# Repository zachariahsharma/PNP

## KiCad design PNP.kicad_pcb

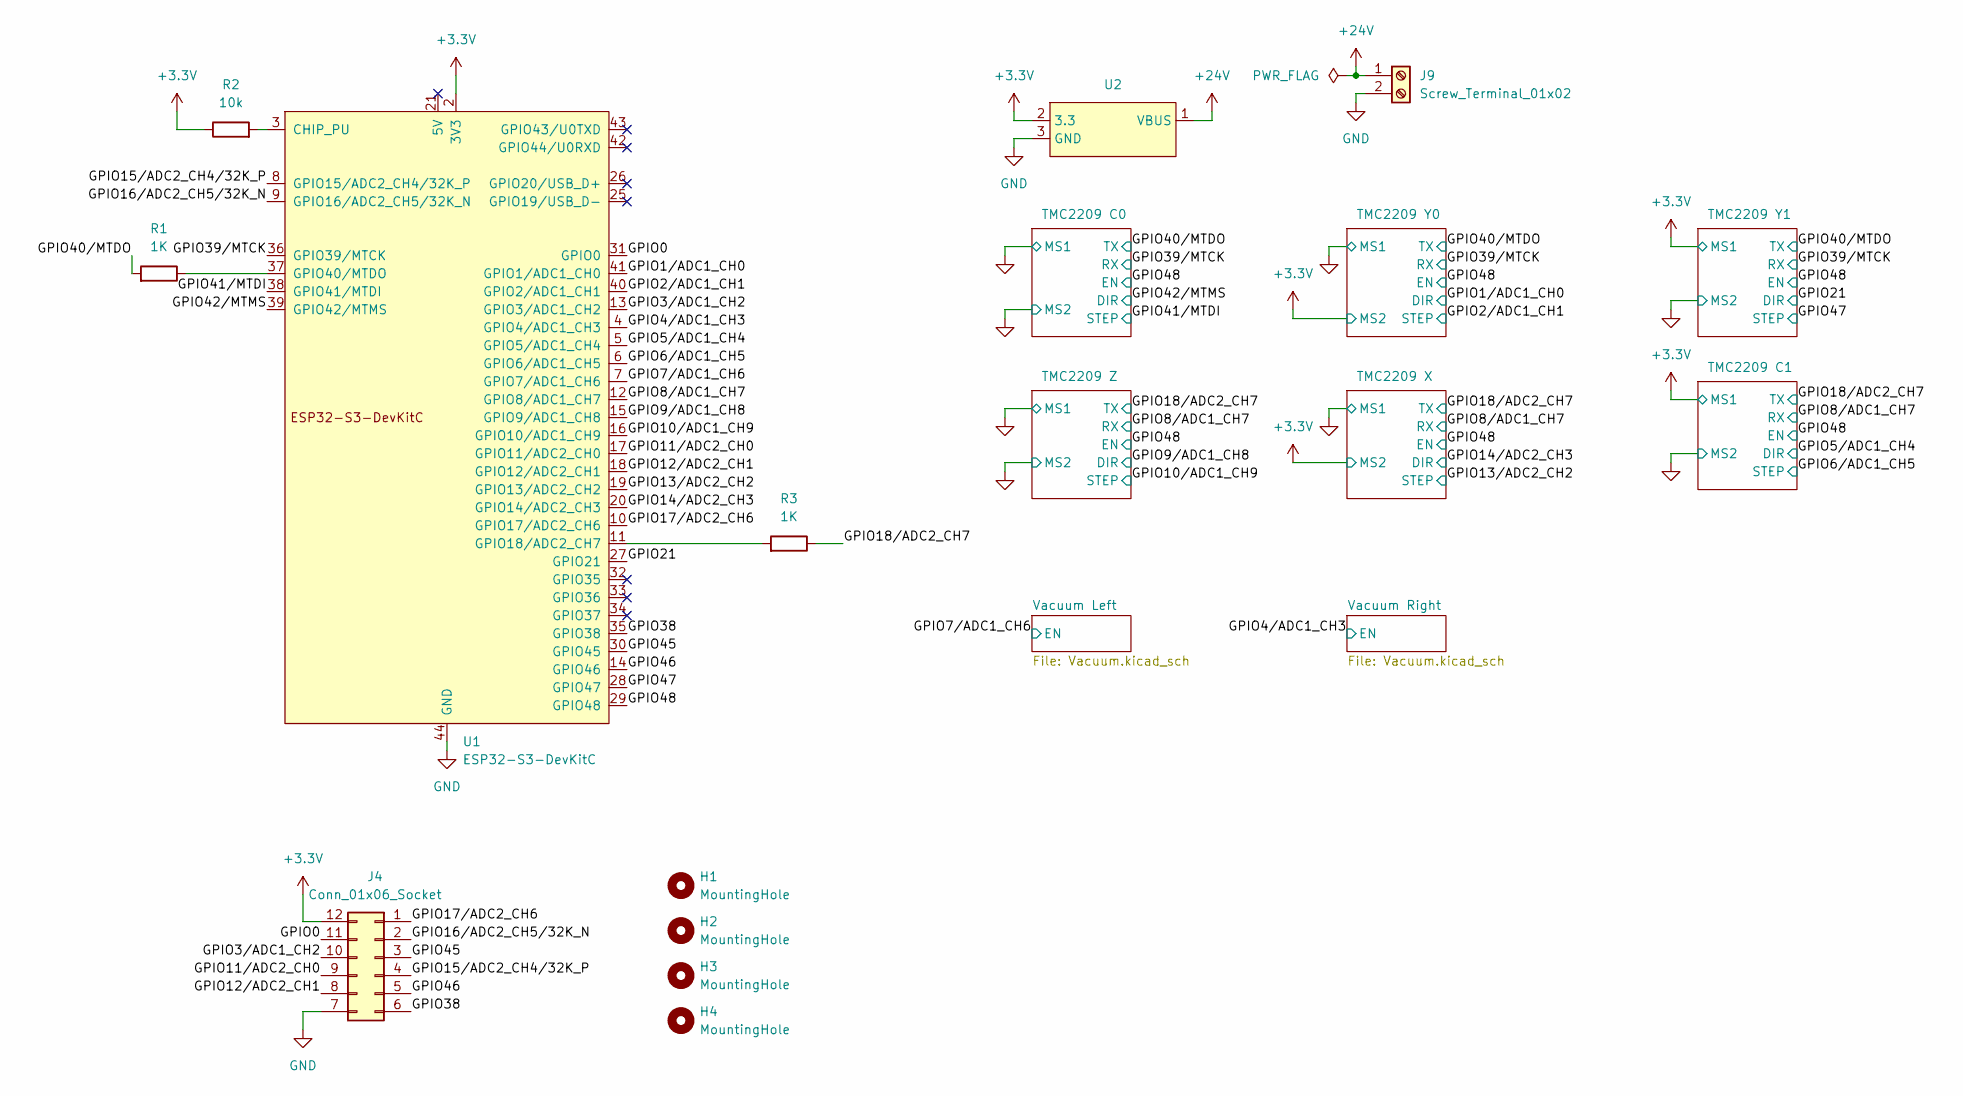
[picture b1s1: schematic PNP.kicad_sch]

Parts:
H1, H2, H3, H4: MountingHole; MountingHole_4.3mm_M4
J4: Conn_01x06_Socket; PinHeader_2x06_P2.54mm_Vertical
J9: Screw_Terminal_01x02; TerminalBlock_Phoenix_MKDS-1,5-2-5.08_1x02_P5.08mm_Horizont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
R1, R3: 1K; R_Axial_DIN0207_L6.3mm_D2.5mm_P7.62mm_Horizontal
R2: 10k; R_Axial_DIN0207_L6.3mm_D2.5mm_P7.62mm_Horizontal
U1: ESP32-S3-DevKitC
U2: Mini MP1584EN Buck Converter Module

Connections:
+3.3V: J4.12, R2.1, U1.1 (3V3), U1.2 (3V3), U2.2 (3.3); also elsewhere on the board
+24V: J9.1, U2.1 (VBUS); also elsewhere on the board
/GPIO0: J4.11, U1.31 (GPIO0)
/GPIO1/ADC1_CH0: U1.41 (GPIO1/ADC1_CH0); also elsewhere on the board
/GPIO2/ADC1_CH1: U1.40 (GPIO2/ADC1_CH1); also elsewhere on the board
/GPIO3/ADC1_CH2: J4.10, U1.13 (GPIO3/ADC1_CH2)
/GPIO4/ADC1_CH3: U1.4 (GPIO4/ADC1_CH3); also elsewhere on the board
/GPIO5/ADC1_CH4: U1.5 (GPIO5/ADC1_CH4); also elsewhere on the board
/GPIO6/ADC1_CH5: U1.6 (GPIO6/ADC1_CH5); also elsewhere on the board
/GPIO7/ADC1_CH6: U1.7 (GPIO7/ADC1_CH6); also elsewhere on the board
/GPIO9/ADC1_CH8: U1.15 (GPIO9/ADC1_CH8); also elsewhere on the board
/GPIO10/ADC1_CH9: U1.16 (GPIO10/ADC1_CH9); also elsewhere on the board
/GPIO11/ADC2_CH0: J4.9, U1.17 (GPIO11/ADC2_CH0)
/GPIO12/ADC2_CH1: J4.8, U1.18 (GPIO12/ADC2_CH1)
/GPIO13/ADC2_CH2: U1.19 (GPIO13/ADC2_CH2); also elsewhere on the board
/GPIO14/ADC2_CH3: U1.20 (GPIO14/ADC2_CH3); also elsewhere on the board
/GPIO15/ADC2_CH4/32K_P: J4.4, U1.8 (GPIO15/ADC2_CH4/32K_P)
/GPIO17/ADC2_CH6: J4.1, U1.10 (GPIO17/ADC2_CH6)
/GPIO18/ADC2_CH7: R3.1, U1.12 (GPIO8/ADC1_CH7); also elsewhere on the board
/GPIO21: U1.27 (GPIO21); also elsewhere on the board
/GPIO38: J4.6, U1.35 (GPIO38)
/GPIO39/MTCK: R1.2, U1.36 (GPIO39/MTCK); also elsewhere on the board
/GPIO41/MTDI: U1.38 (GPIO41/MTDI); also elsewhere on the board
/GPIO42/MTMS: U1.39 (GPIO42/MTMS); also elsewhere on the board
/GPIO45: J4.3, U1.30 (GPIO45)
/GPIO46: J4.5, U1.14 (GPIO46)
/GPIO47: U1.28 (GPIO47); also elsewhere on the board
/GPIO48: U1.29 (GPIO48); also elsewhere on the board
GND: J4.7, J9.2, U1.22 (GND), U1.23 (GND), U1.24 (GND), U1.44 (GND), U2.3 (GND); also elsewhere on the board
unnamed: R2.2, U1.3 (CHIP_PU)
unnamed: R3.2, U1.11 (GPIO18/ADC2_CH7)
unnamed: R1.1, U1.37 (GPIO40/MTDO)

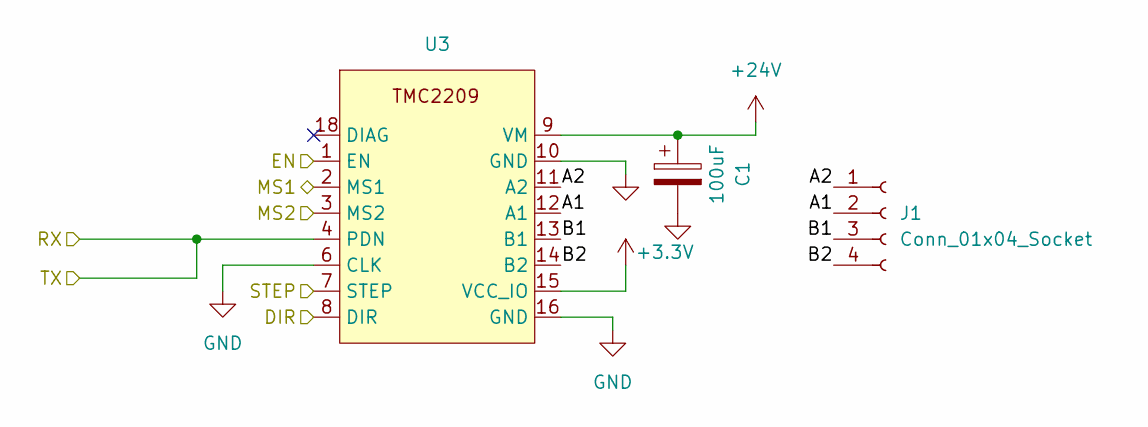
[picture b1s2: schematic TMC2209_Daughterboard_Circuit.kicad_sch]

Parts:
C1: 100uF; CP_Radial_D8.0mm_P3.50mm
J1: Conn_01x04_Socket; JST_EH_B4B-EH-A_1x04_P2.50mm_Vertical
U3: TMC2209 V1.3

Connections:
+3.3V: U3.3 (MS2), U3.15 (VCC_IO); also elsewhere on the board
+24V: C1.1, U3.9 (VM); also elsewhere on the board
/GPIO13/ADC2_CH2: U3.7 (STEP); also elsewhere on the board
/GPIO14/ADC2_CH3: U3.8 (DIR); also elsewhere on the board
/GPIO18/ADC2_CH7: U3.4 (PDN); also elsewhere on the board
/GPIO48: U3.1 (EN); also elsewhere on the board
/TMC2209 X/A1: J1.2, U3.12 (A1)
/TMC2209 X/A2: J1.1, U3.11 (A2)
/TMC2209 X/B1: J1.3, U3.13 (B1)
/TMC2209 X/B2: J1.4, U3.14 (B2)
GND: C1.2, U3.2 (MS1), U3.6 (CLK), U3.10 (GND), U3.16 (GND); also elsewhere on the board

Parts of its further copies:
C2, C3, C4, C5, C6: 100uF; CP_Radial_D8.0mm_P3.50mm
J2, J3, J5, J6, J7: Conn_01x04_Socket; JST_EH_B4B-EH-A_1x04_P2.50mm_Vertical

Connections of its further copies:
+24V: C2.1, C3.1, C4.1, C5.1, C6.1; also elsewhere on the board
/TMC2209 C0/A1: J6.2; also elsewhere on the board
/TMC2209 C0/A2: J6.1; also elsewhere on the board
/TMC2209 C0/B1: J6.3; also elsewhere on the board
/TMC2209 C0/B2: J6.4; also elsewhere on the board
/TMC2209 C1/A1: J7.2; also elsewhere on the board
/TMC2209 C1/A2: J7.1; also elsewhere on the board
/TMC2209 C1/B1: J7.3; also elsewhere on the board
/TMC2209 C1/B2: J7.4; also elsewhere on the board
/TMC2209 Y0/A1: J2.2; also elsewhere on the board
/TMC2209 Y0/A2: J2.1; also elsewhere on the board
/TMC2209 Y0/B1: J2.3; also elsewhere on the board
/TMC2209 Y0/B2: J2.4; also elsewhere on the board
/TMC2209 Y1/A1: J3.2; also elsewhere on the board
/TMC2209 Y1/A2: J3.1; also elsewhere on the board
/TMC2209 Y1/B1: J3.3; also elsewhere on the board
/TMC2209 Y1/B2: J3.4; also elsewhere on the board
/TMC2209 Z/A1: J5.2; also elsewhere on the board
/TMC2209 Z/A2: J5.1; also elsewhere on the board
/TMC2209 Z/B1: J5.3; also elsewhere on the board
/TMC2209 Z/B2: J5.4; also elsewhere on the board
GND: C2.2, C3.2, C4.2, C5.2, C6.2; also elsewhere on the board

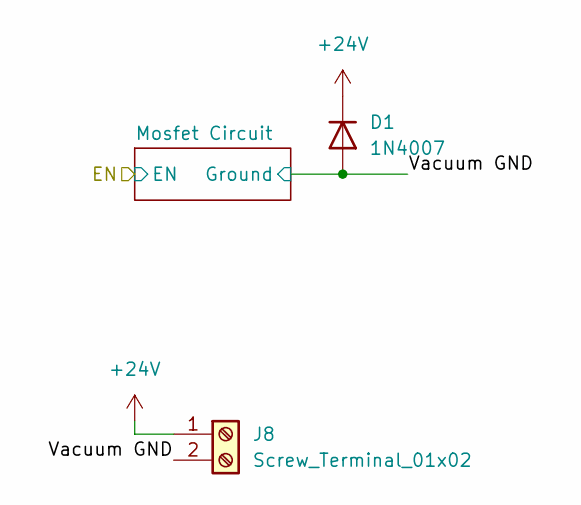
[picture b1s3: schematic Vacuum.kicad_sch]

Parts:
D1: 1N4007; D_DO-41_SOD81_P10.16mm_Horizontal
J8: Screw_Terminal_01x02; TerminalBlock_Phoenix_MKDS-1,5-2-5.08_1x02_P5.08mm_Horizont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

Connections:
+24V: D1.1 (K), J8.1; also elsewhere on the board
/Vacuum Left/Vacuum GND: D1.2 (A), J8.2; also elsewhere on the board

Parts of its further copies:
D2: 1N4007; D_DO-41_SOD81_P10.16mm_Horizontal
J10: Screw_Terminal_01x02; TerminalBlock_Phoenix_MKDS-1,5-2-5.08_1x02_P5.08mm_Horizont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

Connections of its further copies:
+24V: D2.1 (K), J10.1; also elsewhere on the board
/Vacuum Right/Vacuum GND: D2.2 (A), J10.2; also elsewhere on the board

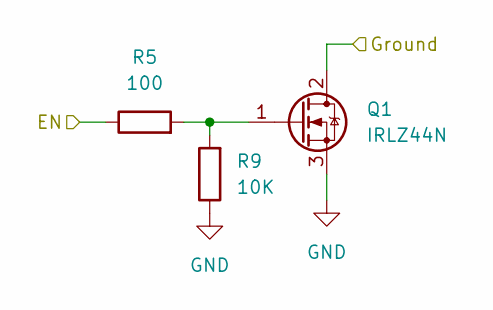
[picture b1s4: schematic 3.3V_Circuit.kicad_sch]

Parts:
Q1: IRLZ44N; TO-220-3_Vertical
R5: 100; R_Axial_DIN0207_L6.3mm_D2.5mm_P7.62mm_Horizontal
R9: 10K; R_Axial_DIN0207_L6.3mm_D2.5mm_P7.62mm_Horizontal

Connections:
/GPIO7/ADC1_CH6: R5.1; also elsewhere on the board
/Vacuum Left/Vacuum GND: Q1.2 (D); also elsewhere on the board
GND: Q1.3 (S), R9.1; also elsewhere on the board
unnamed: Q1.1 (G), R5.2, R9.2

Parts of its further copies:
Q3: IRLZ44N; TO-220-3_Vertical
R12: 100; R_Axial_DIN0207_L6.3mm_D2.5mm_P7.62mm_Horizontal
R13: 10K; R_Axial_DIN0207_L6.3mm_D2.5mm_P7.62mm_Horizontal

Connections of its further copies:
/GPIO4/ADC1_CH3: R12.1; also elsewhere on the board
/Vacuum Right/Vacuum GND: Q3.2 (D); also elsewhere on the board
GND: Q3.3 (S), R13.1; also elsewhere on the board
unnamed: Q3.1 (G), R12.2, R13.2

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
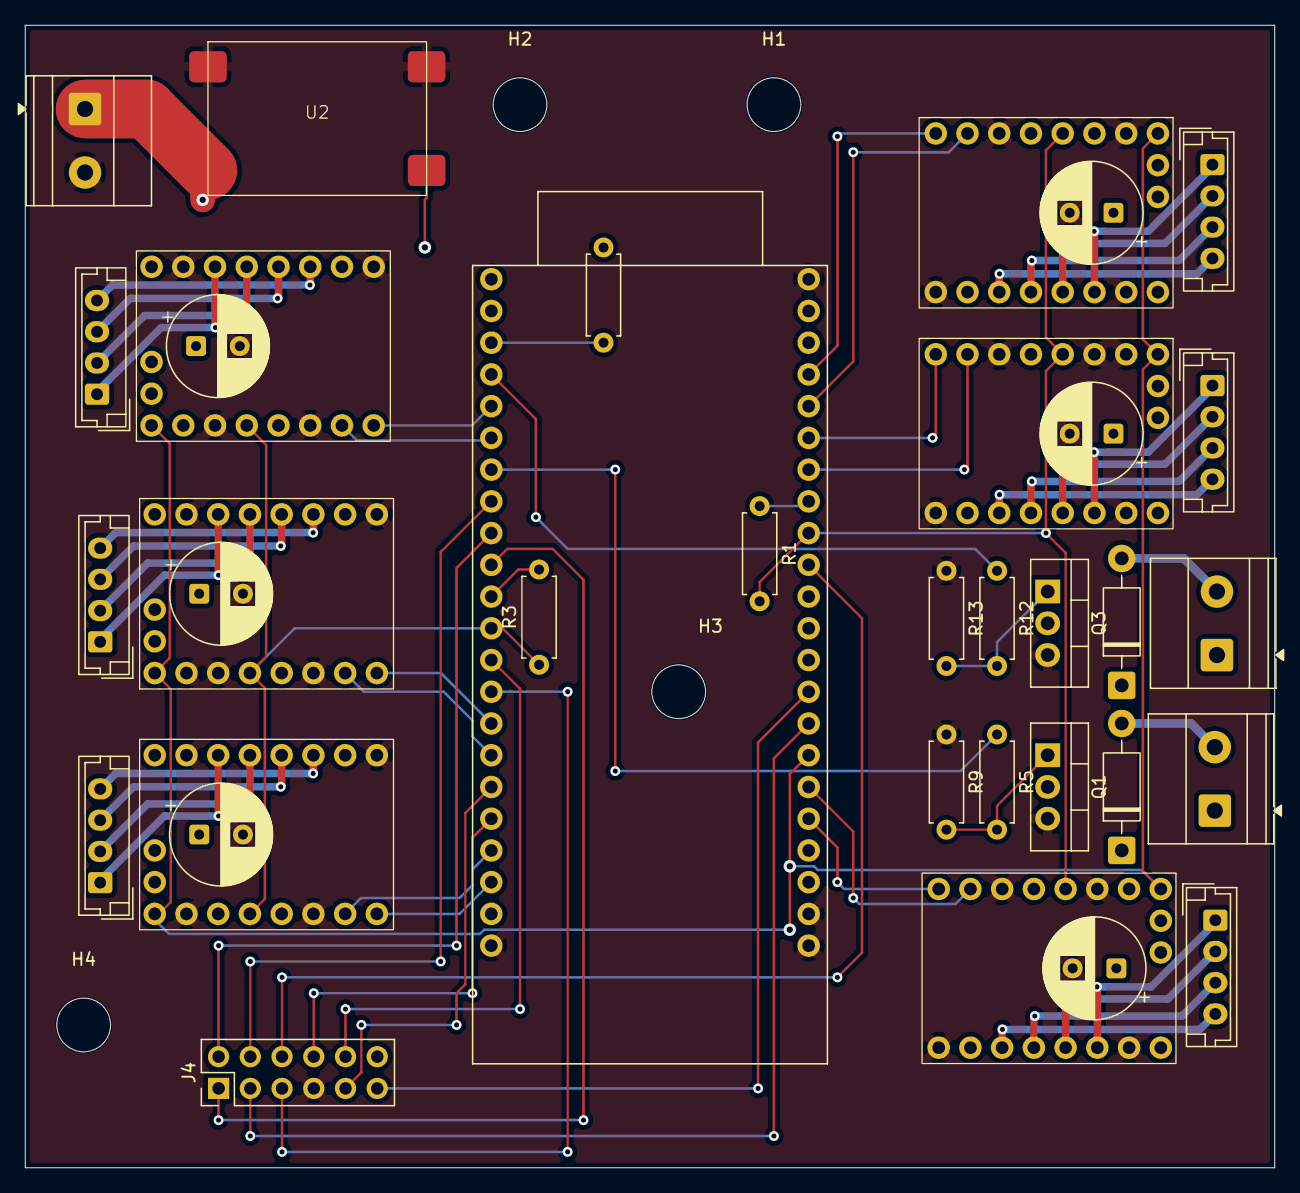
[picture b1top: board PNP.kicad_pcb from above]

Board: 4 copper layers, 100.0 x 91.4 mm, 39 parts (0 on the bottom side), 61 nets.

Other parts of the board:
U4, U5, U7, U8, U9: TMC2209 V1.3

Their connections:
+3.3V: U4.3 (MS2), U4.15 (VCC_IO), U5.2 (MS1), U5.15 (VCC_IO), U7.15 (VCC_IO), U8.15 (VCC_IO), U9.2 (MS1), U9.15 (VCC_IO); also elsewhere on the board
+24V: U4.9 (VM), U5.9 (VM), U7.9 (VM), U8.9 (VM), U9.9 (VM); also elsewhere on the board
/GPIO1/ADC1_CH0: U4.8 (DIR); also elsewhere on the board
/GPIO2/ADC1_CH1: U4.7 (STEP); also elsewhere on the board
/GPIO5/ADC1_CH4: U9.8 (DIR); also elsewhere on the board
/GPIO6/ADC1_CH5: U9.7 (STEP); also elsewhere on the board
/GPIO9/ADC1_CH8: U7.8 (DIR); also elsewhere on the board
/GPIO10/ADC1_CH9: U7.7 (STEP); also elsewhere on the board
/GPIO18/ADC2_CH7: U7.4 (PDN), U9.4 (PDN); also elsewhere on the board
/GPIO21: U5.8 (DIR); also elsewhere on the board
/GPIO39/MTCK: U4.4 (PDN), U5.4 (PDN), U8.4 (PDN); also elsewhere on the board
/GPIO41/MTDI: U8.7 (STEP); also elsewhere on the board
/GPIO42/MTMS: U8.8 (DIR); also elsewhere on the board
/GPIO47: U5.7 (STEP); also elsewhere on the board
/GPIO48: U4.1 (EN), U5.1 (EN), U7.1 (EN), U8.1 (EN), U9.1 (EN); also elsewhere on the board
/TMC2209 C0/A1: U8.12 (A1); also elsewhere on the board
/TMC2209 C0/A2: U8.11 (A2); also elsewhere on the board
/TMC2209 C0/B1: U8.13 (B1); also elsewhere on the board
/TMC2209 C0/B2: U8.14 (B2); also elsewhere on the board
/TMC2209 C1/A1: U9.12 (A1); also elsewhere on the board
/TMC2209 C1/A2: U9.11 (A2); also elsewhere on the board
/TMC2209 C1/B1: U9.13 (B1); also elsewhere on the board
/TMC2209 C1/B2: U9.14 (B2); also elsewhere on the board
/TMC2209 Y0/A1: U4.12 (A1); also elsewhere on the board
/TMC2209 Y0/A2: U4.11 (A2); also elsewhere on the board
/TMC2209 Y0/B1: U4.13 (B1); also elsewhere on the board
/TMC2209 Y0/B2: U4.14 (B2); also elsewhere on the board
/TMC2209 Y1/A1: U5.12 (A1); also elsewhere on the board
/TMC2209 Y1/A2: U5.11 (A2); also elsewhere on the board
/TMC2209 Y1/B1: U5.13 (B1); also elsewhere on the board
/TMC2209 Y1/B2: U5.14 (B2); also elsewhere on the board
/TMC2209 Z/A1: U7.12 (A1); also elsewhere on the board
/TMC2209 Z/A2: U7.11 (A2); also elsewhere on the board
/TMC2209 Z/B1: U7.13 (B1); also elsewhere on the board
/TMC2209 Z/B2: U7.14 (B2); also elsewhere on the board
GND: U4.2 (MS1), U4.6 (CLK), U4.10 (GND), U4.16 (GND), U5.3 (MS2), U5.6 (CLK), U5.10 (GND), U5.16 (GND), U7.2 (MS1), U7.3 (MS2), U7.6 (CLK), U7.10 (GND), U7.16 (GND), U8.2 (MS1), U8.3 (MS2), U8.6 (CLK), U8.10 (GND), U8.16 (GND), U9.3 (MS2), U9.6 (CLK), U9.10 (GND), U9.16 (GND); also elsewhere on the board

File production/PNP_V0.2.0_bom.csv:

Designator,Footprint,Quantity,Value,LCSC Part #
"C1, C2, C3, C4, C5, C6",CP_Radial_D8.0mm_P3.50mm,6,100uF,
"D1, D2",D_DO-41_SOD81_P10.16mm_Horizontal,2,1N4007,
"J1, J2, J3, J5, J6, J7",JST_EH_B4B-EH-A_1x04_P2.50mm_Vertical,6,Conn_01x04_Socket,
"J10, J8, J9","TerminalBlock_Phoenix_MKDS-1,5-2-5.08_1x02_P5.08mm_Horizontal",3,Screw_Terminal_01x02,
J4,PinHeader_2x06_P2.54mm_Vertical,1,Conn_01x06_Socket,
"Q1, Q3",TO-220-3_Vertical,2,IRLZ44N,
"R1, R3",R_Axial_DIN0207_L6.3mm_D2.5mm_P7.62mm_Horizontal,2,1K,
"R12, R5",R_Axial_DIN0207_L6.3mm_D2.5mm_P7.62mm_Horizontal,2,100,
"R13, R2, R9",R_Axial_DIN0207_L6.3mm_D2.5mm_P7.62mm_Horizontal,3,10K,
U1,ESP32-S3-DevKitC,1,ESP32-S3-DevKitC,
U2,Mini MP1584EN Buck Converter Module,1,~,
"U3, U4, U5, U7, U8, U9",TMC2209 V1.3,6,~,

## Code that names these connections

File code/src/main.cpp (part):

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 * No USB needed while running (avoids the 24V-vs-USB 3.3V contention). Flash with
 * USB only while the 24 V is OFF.
 *
 * Axes (traced from PNP.kicad_pcb). EN = GPIO48 (global, held low; per-axis on/off
 * via TMC `toff`). Two UART buses; address set by each socket's MS1/MS2 straps:
 *   Bus A RX=GPIO8, TX=GPIO18 (1k series R):  C1=addr1(step6,dir5)  Z=addr0(step10,dir9)  X=addr2(step13,dir14)
 *   Bus B RX=GPIO39, TX=GPIO40 (1k series R): Y0=addr2(step2,dir1) Y1=addr1(step47,dir21) C0=addr0(step41,dir42)
 *
 * Step/dir pulses: FastAccelStepper (hardware-timed, with acceleration + bounded
 * "move N turns"). Current/microstep/chopper: TMC2209 over UART.
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function renderVac(){
 document.getElementById('vacwrap').innerHTML=`
  <div class="card"><h2>Vacuum</h2>
   <div class="row"><label>Vacuum Left (GPIO4)</label>
    <div class="toggle"><button id="vl0">OFF</button><button id="vl1">ON</button></div></div>
   <div class="row"><label>Vacuum Right (GPIO7)</label>
    <div class="toggle"><button id="vr0">OFF</button><button id="vr1">ON</button></div></div>
  </div>`;
 const vl0=gid('vl0'),vl1=gid('vl1'),vr0=gid('vr0'),vr1=gid('vr1');
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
